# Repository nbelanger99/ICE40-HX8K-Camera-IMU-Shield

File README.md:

# ICE40-HX8K Camera & IMU Shield

This is an open-source shield designed for Lattice's [ICE-40 breakout board](http://www.latticesemi.com/en/Products/DevelopmentBoardsAndKits/iCE40HX8KBreakoutBoard.aspx) which has a single OV7690 & an IMU. It was developed to experiment with a hardware-accelerated Mono-SLAM algorithm, or other vision applications

As of yet; the verilog library needed to test the design has **not** been written. If a working module is developed, an [ICEStorm](https://github.com/YosysHQ/icestorm) project example will be open sourced and linked here. 

<br>

<br>

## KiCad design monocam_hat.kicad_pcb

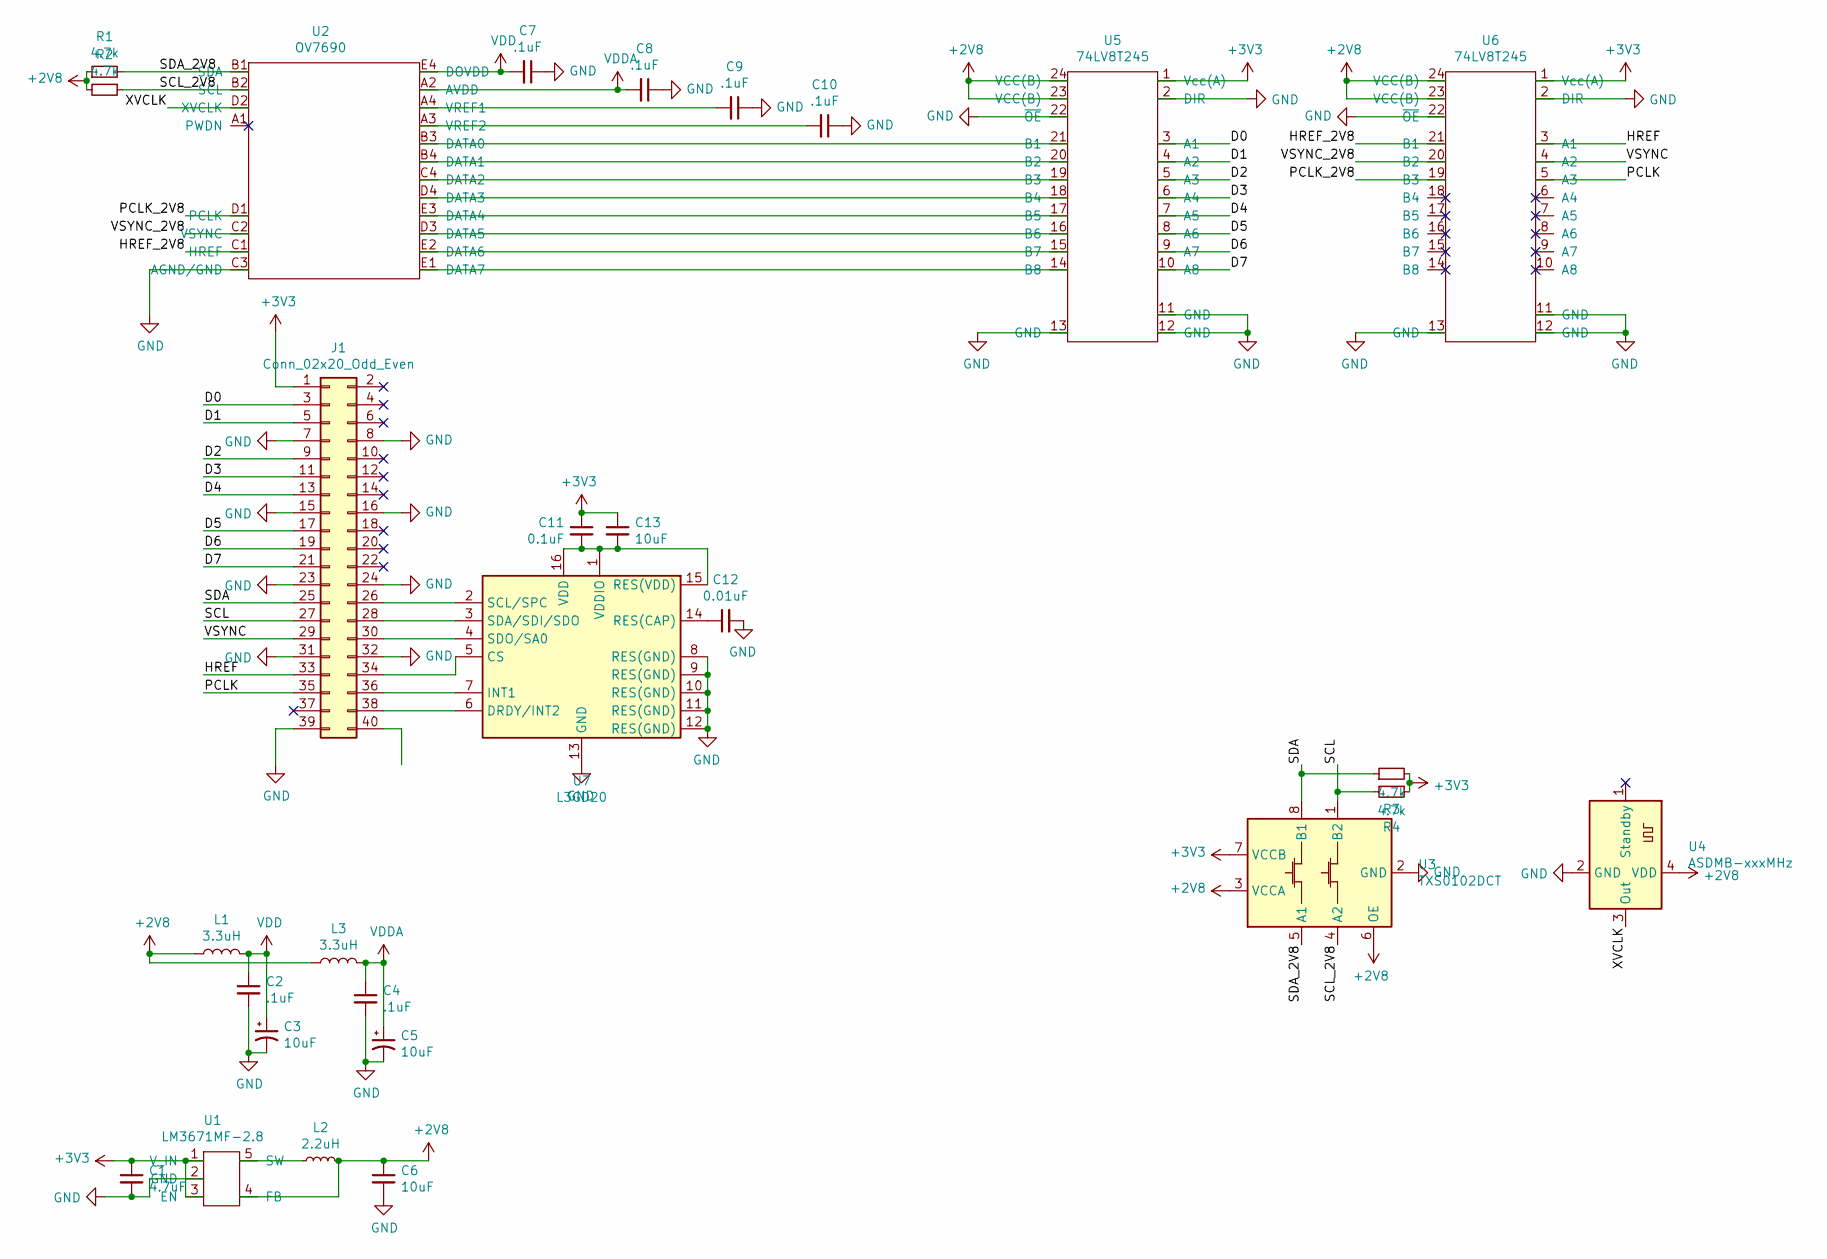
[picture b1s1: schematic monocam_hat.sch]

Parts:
C1: 4.7uF; C_0402_1005Metric
C2, C4, C7, C8, C9, C10: .1uF; C_0402_1005Metric
C3, C5, C6, C13: 10uF; C_0402_1005Metric
C11: 0.1uF; C_0402_1005Metric
C12: 0.01uF; C_0402_1005Metric
J1: Conn_02x20_Odd_Even; PinHeader_2x20_P2.54mm_Vertical
L1, L3: 3.3uH; L_0603_1608Metric
L2: 2.2uH; L_0603_1608Metric
R1, R2, R3, R4: 4.7k; R_0402_1005Metric
U1: LM3671MF-2.8; SOT-23-5
U2: OV7690; BGA-20_2.4x2.6mm_Layout4x5_P0.5mm_0.2mm_Pad
U3: TXS0102DCT; SSOP-8_2.95x2.8mm_P0.65mm
U4: ASDMB-xxxMHz; Oscillator_SMD_Abracon_ASDMB-4Pin_2.5x2.0mm
U5, U6: 74LV8T245; TSSOP-24_4.4x7.8mm_P0.65mm
U7: L3GD20; LGA-16_4x4mm_P0.65mm_LayoutBorder4x4y

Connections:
+2V8: C6.1, L1.1, L2.2, L3.1, R1.1, R2.2, U1.4 (FB), U3.3 (VCCA), U3.6 (OE), U4.4 (VDD), U5.23 (VCC(B)), U5.24 (VCC(B)), U6.23 (VCC(B)), U6.24 (VCC(B))
+3V3: C1.1, C11.1, C13.1, J1.1, R3.2, R4.1, U1.1 (V_IN), U1.3 (EN), U3.7 (VCCB), U5.1 (Vcc(A)), U6.1 (Vcc(A))
/D0: J1.3, U5.3 (A1)
/D1: J1.5, U5.4 (A2)
/D2: J1.9, U5.5 (A3)
/D3: J1.11, U5.6 (A4)
/D4: J1.13, U5.7 (A5)
/D5: J1.17, U5.8 (A6)
/D6: J1.19, U5.9 (A7)
/D7: J1.21, U5.10 (A8)
/HREF: J1.33, U6.3 (A1)
/HREF_2V8: U2.C1 (HREF), U6.21 (B1)
/PCLK: J1.35, U6.5 (A3)
/PCLK_2V8: U2.D1 (PCLK), U6.19 (B3)
/SCL: J1.27, R4.2, U3.1 (B2)
/SCL_2V8: R2.1, U2.B2 (SCL), U3.4 (A2)
/SDA: J1.25, R3.1, U3.8 (B1)
/SDA_2V8: R1.2, U2.B1 (SDA), U3.5 (A1)
/VSYNC: J1.29, U6.4 (A2)
/VSYNC_2V8: U2.C2 (VSYNC), U6.20 (B2)
/XVCLK: U2.D2 (XVCLK), U4.3 (Out)
GND: C1.2, C2.2, C3.2, C4.2, C5.2, C6.2, C7.1, C8.1, C9.1, C10.1, C12.2, J1.7, J1.8, J1.15, J1.16, J1.23, J1.24, J1.31, J1.32, J1.39, U1.2 (GND), U2.C3 (AGND/GND), U3.2 (GND), U4.2 (GND), U5.2 (DIR), U5.11 (GND), U5.12 (GND), U5.13 (GND), U5.22 (~OE), U6.2 (DIR), U6.11 (GND), U6.12 (GND), U6.13 (GND), U6.22 (~OE), U7.8 (RES(GND)), U7.9 (RES(GND)), U7.10 (RES(GND)), U7.11 (RES(GND)), U7.12 (RES(GND)), U7.13 (GND)
unnamed: C9.2, U2.A4 (VREF1)
unnamed: C10.2, U2.A3 (VREF2)
unnamed: C11.2, C13.2, U7.1 (VDDIO), U7.15 (RES(VDD)), U7.16 (VDD)
unnamed: C12.1, U7.14 (RES(CAP))
unnamed: J1.26, U7.2 (SCL/SPC)
unnamed: J1.28, U7.3 (SDA/SDI/SDO)
unnamed: J1.30, U7.4 (SDO/SA0)
unnamed: J1.34, U7.5 (CS)
unnamed: J1.36, U7.7 (INT1)
unnamed: J1.38, U7.6 (DRDY/INT2)
unnamed: L2.1, U1.5 (SW)
unnamed: U2.B3 (DATA0), U5.21 (B1)
unnamed: U2.B4 (DATA1), U5.20 (B2)
unnamed: U2.C4 (DATA2), U5.19 (B3)
unnamed: U2.D3 (DATA5), U5.16 (B6)
unnamed: U2.D4 (DATA3), U5.18 (B4)
unnamed: U2.E1 (DATA7), U5.14 (B8)
unnamed: U2.E2 (DATA6), U5.15 (B7)
unnamed: U2.E3 (DATA4), U5.17 (B5)
VDD: C2.1, C3.1, C7.2, L1.2, U2.E4 (DOVDD)
VDDA: C4.1, C5.1, C8.2, L3.2, U2.A2 (AVDD)

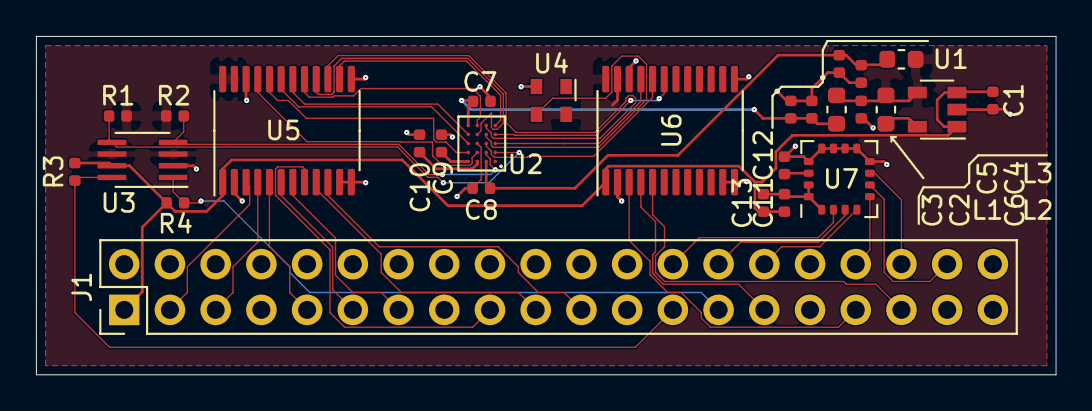
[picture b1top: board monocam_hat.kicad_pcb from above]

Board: 2 copper layers, 56.6 x 18.8 mm, 28 parts (0 on the bottom side), 43 nets.

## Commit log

2020-08-31 v1 layout complete
2021-02-10 Removing tracked gerbers and adding gitignore
2021-02-10 V2 layout complete
2021-02-10 Adding media & docs
2021-02-10 Updating readme images
